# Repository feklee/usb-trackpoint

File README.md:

Introduction
============

Electronics Arduino project, to connect an IBM TrackPoint as an external
pointing device via USB.

Features:

  * TrackPoint fully works, incl. buttons.

  * Adjustable sensitivity with potentiometer.

  * Middle button scrolling.

  * An RGB LED cycles, showing how the program loops.

Circuit
=======

![Photos of circuit, front and back][4]

For the schematic, see the included [EAGLE][2] project.

The PS/2 connection is done with a detachable cable. This allows:

  * testing the Arduino code with an external PS/2 mouse,
  
  * using the TrackPoint as a PS/2 mouse directly on a computer (didn't get
    that to work).

Some components were recycled:

  * TrackPoint board: Broken off from the keyboard of an iSeries 1200
    (1161-267), my first ThinkPad (bought in 2000).

  * Button switches: Taken from an old Logitech mouse.
  
  * PS/2 cable: Cut off an old and broken Cherry keyboard.
  
  * Back metal plate: From the keyboard that provided the TrackPoint board.
  
  * Front metal plate: Cut from a plate found inside a ThinkPad X41, then
    drilled.
  
  * M2 screws: From some ThinkPad.
  
  * M2 nuts: Insert nuts found in ThinkPad X41 plastic parts.

For cycling the RGB LED, a decade counter is used, partly as an exercise for
the author.

Arduino code
============

See comments at top of `.ino` file.

Trackpoint PCB
==============

To figure out the pinout of the TrackPoint PCB, the key steps were:

  * I looked at the FFC connecting the ThinkPad's mainboard, the keyboard, and
    the TrackPoint:
    
      + Two wires were dimensioned wider: power supply
      
      + Three lines lead into the keyboard: TrackPoint buttons

  * Using a multimeter and the ThinkPad turned on, I checked the voltage of the
    power supply wires in the FFC: One is ground, one +5V.

  * I connected the broken off board using individual wires to the ThinkPad. By
    trial and error, I figured out that in addition to the power supply, three
    wires are needed (CLK, DATA, RESET).
    
    Fortunately, the keyboard/TrackPoint FCB receptacles in this ThinkPad are
    big enough to hold the FFC plus 0.3 mm copper wire.

  * With the TrackPoint board connected to an Arduino, I figured out by trial
    and error:
    
      + Which wire is CLK, which one is DATA, and which one is RESET?
      
      + Which of the button wires is for LEFT, which one for RIGHT, which one
        for MIDDLE?

TrackPoint PCB soldered to board with 0.3 mm enameled copper wire:

![Photo of TrackPoint on board][1]

License
=======

Copyright (C) 2013 [Felix E. Klee](mailto:felix.klee@inka.de)

Permission is hereby granted, free of charge, to any person obtaining a copy of
this software and associated documentation files (the "Software"), to deal in
the Software without restriction, including without limitation the rights to
use, copy, modify, merge, publish, distribute, sublicense, and/or sell copies
of the Software, and to permit persons to whom the Software is furnished to do
so, subject to the following conditions:

The above copyright notice and this permission notice shall be included in all
copies or substantial portions of the Software.

THE SOFTWARE IS PROVIDED "AS IS", WITHOUT WARRANTY OF ANY KIND, EXPRESS OR
IMPLIED, INCLUDING BUT NOT LIMITED TO THE WARRANTIES OF MERCHANTABILITY,
FITNESS FOR A PARTICULAR PURPOSE AND NONINFRINGEMENT. IN NO EVENT SHALL THE
AUTHORS OR COPYRIGHT HOLDERS BE LIABLE FOR ANY CLAIM, DAMAGES OR OTHER
LIABILITY, WHETHER IN AN ACTION OF CONTRACT, TORT OR OTHERWISE, ARISING FROM,
OUT OF OR IN CONNECTION WITH THE SOFTWARE OR THE USE OR OTHER DEALINGS IN THE
SOFTWARE.

[1]: images/2013-08-16+02_TrackPoint_annotated.png
[2]: http://en.wikipedia.org/wiki/EAGLE
[3]: https://github.com/feklee/arduino-trackpoint
[4]: images/2013-08-16+02_circuit.jpg

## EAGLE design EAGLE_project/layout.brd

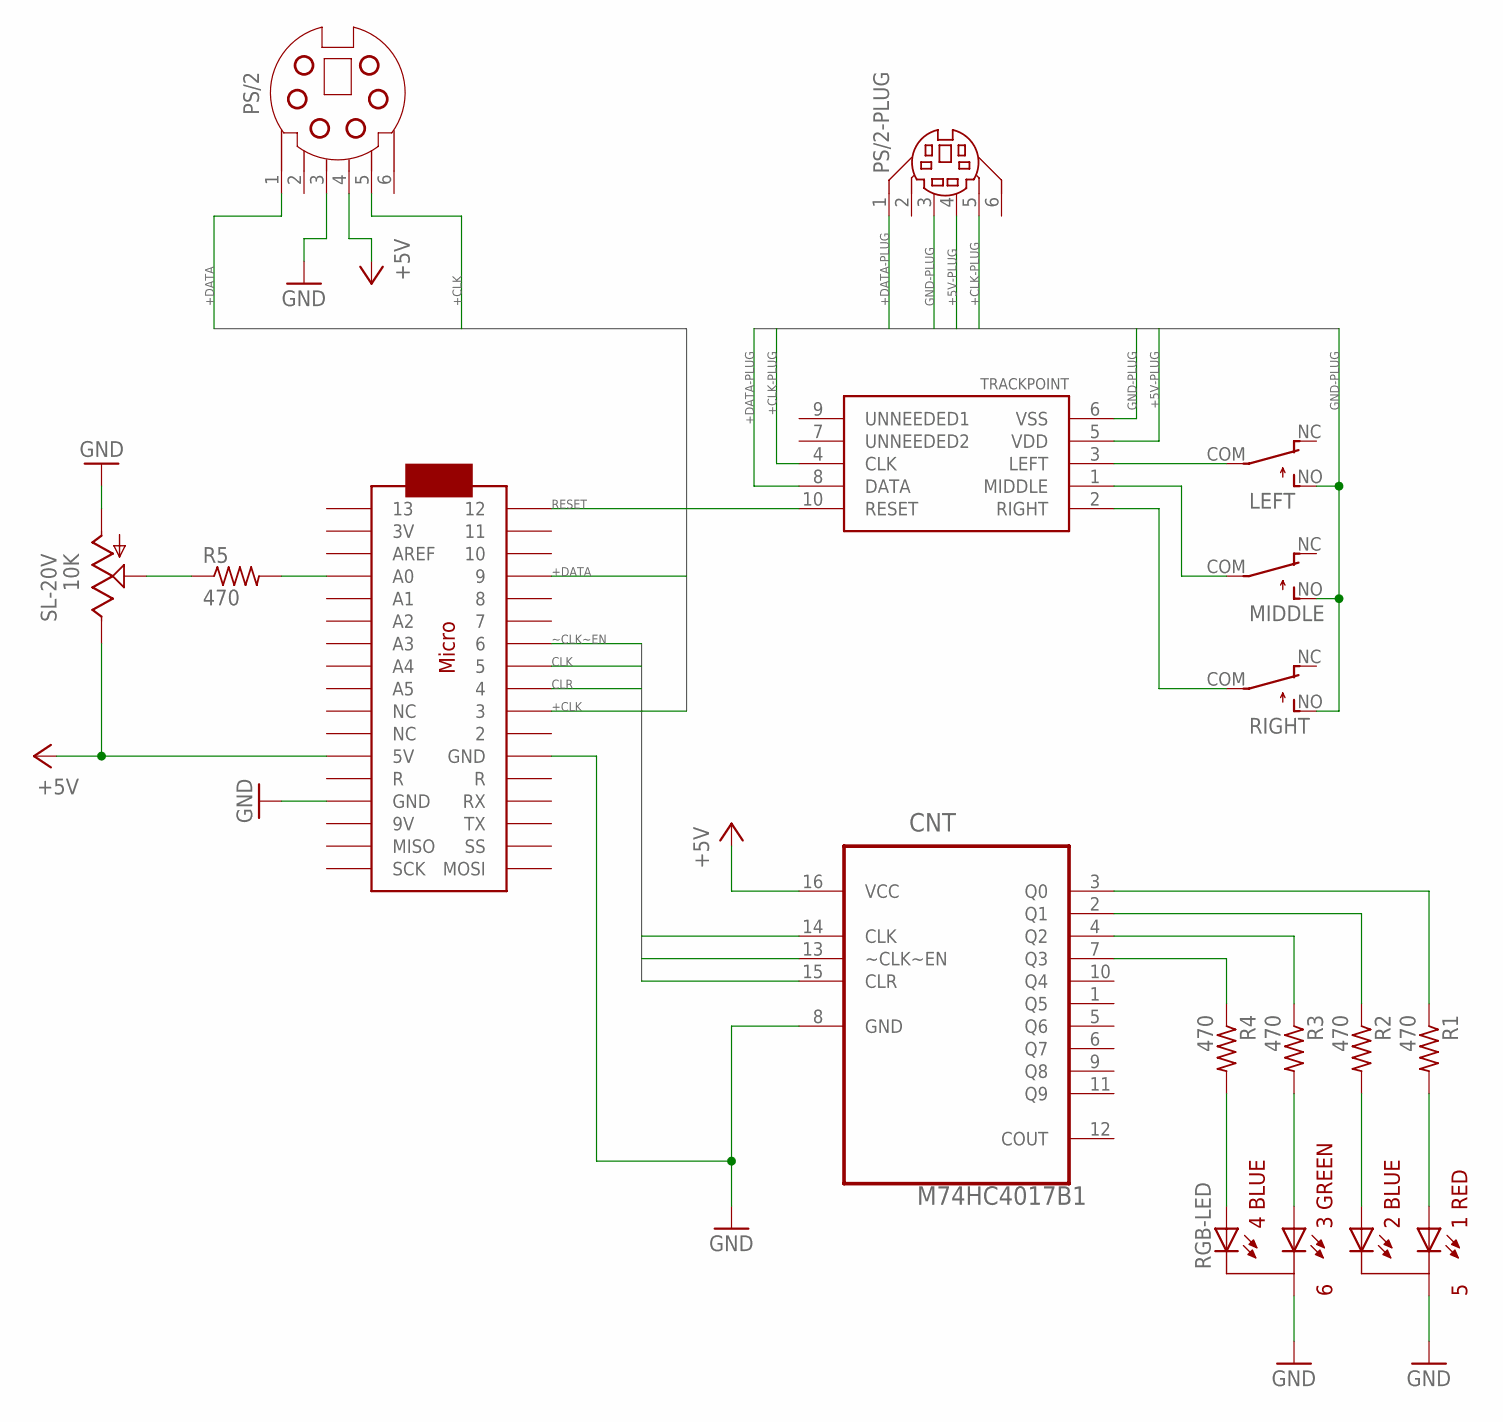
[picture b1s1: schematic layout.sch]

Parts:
CNT: M74HC4017B1; DIP254P762X510-16
PS/2: SSV-BC06
PS/2-PLUG: MDIN06K
R1, R2, R3, R4, R5: 470; 0207/10
RGB-LED: RGBLED; RGBLED5MM
TRACKPOINT: BOARD
U$1: LEFT; D2F
U$2: ARDUINOMICRO
U$3: MIDDLE; D2F
U$5: RIGHT; D2F
U$6: 10K; SL-20V

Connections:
+5V: CNT.16 (VCC), PS/2.4, U$2.P$23 (5V), U$6.4 (E)
+5V-PLUG: PS/2-PLUG.4, TRACKPOINT.5 (VDD)
+CLK: PS/2.5, U$2.P$10 (3)
+CLK-PLUG: PS/2-PLUG.5, TRACKPOINT.4 (CLK)
+DATA: PS/2.1, U$2.P$4 (9)
+DATA-PLUG: PS/2-PLUG.1, TRACKPOINT.8 (DATA)
CLK: CNT.14 (CLK), U$2.P$8 (5)
CLR: CNT.15 (CLR), U$2.P$9 (4)
GND: CNT.8 (GND), PS/2.3, RGB-LED.C5, RGB-LED.C6, U$2.P$12 (GND), U$2.P$21 (GND), U$6.1 (A)
GND-PLUG: PS/2-PLUG.3, TRACKPOINT.6 (VSS), U$1.NO (S), U$3.NO (S), U$5.NO (S)
LED: R4.2, RGB-LED.A4_BLUE
LEFT: TRACKPOINT.3 (LEFT), U$1.COM
unnamed: CNT.2 (Q1), R2.1
unnamed: CNT.3 (Q0), R1.1
unnamed: CNT.4 (Q2), R3.1
unnamed: CNT.7 (Q3), R4.1
unnamed: R5.2, U$2.P$31 (A0)
unnamed: R3.2, RGB-LED.A3_GREEN
unnamed: R2.2, RGB-LED.A2_BLUE
unnamed: R1.2, RGB-LED.A1_RED
unnamed: TRACKPOINT.1 (MIDDLE), U$3.COM
unnamed: TRACKPOINT.2 (RIGHT), U$5.COM
unnamed: R5.1, U$6.2 (S), U$6.3 (S)
RESET: TRACKPOINT.10 (RESET), U$2.P$1 (12)
~CLK~EN: CNT.13 (~CLK~EN), U$2.P$7 (6)

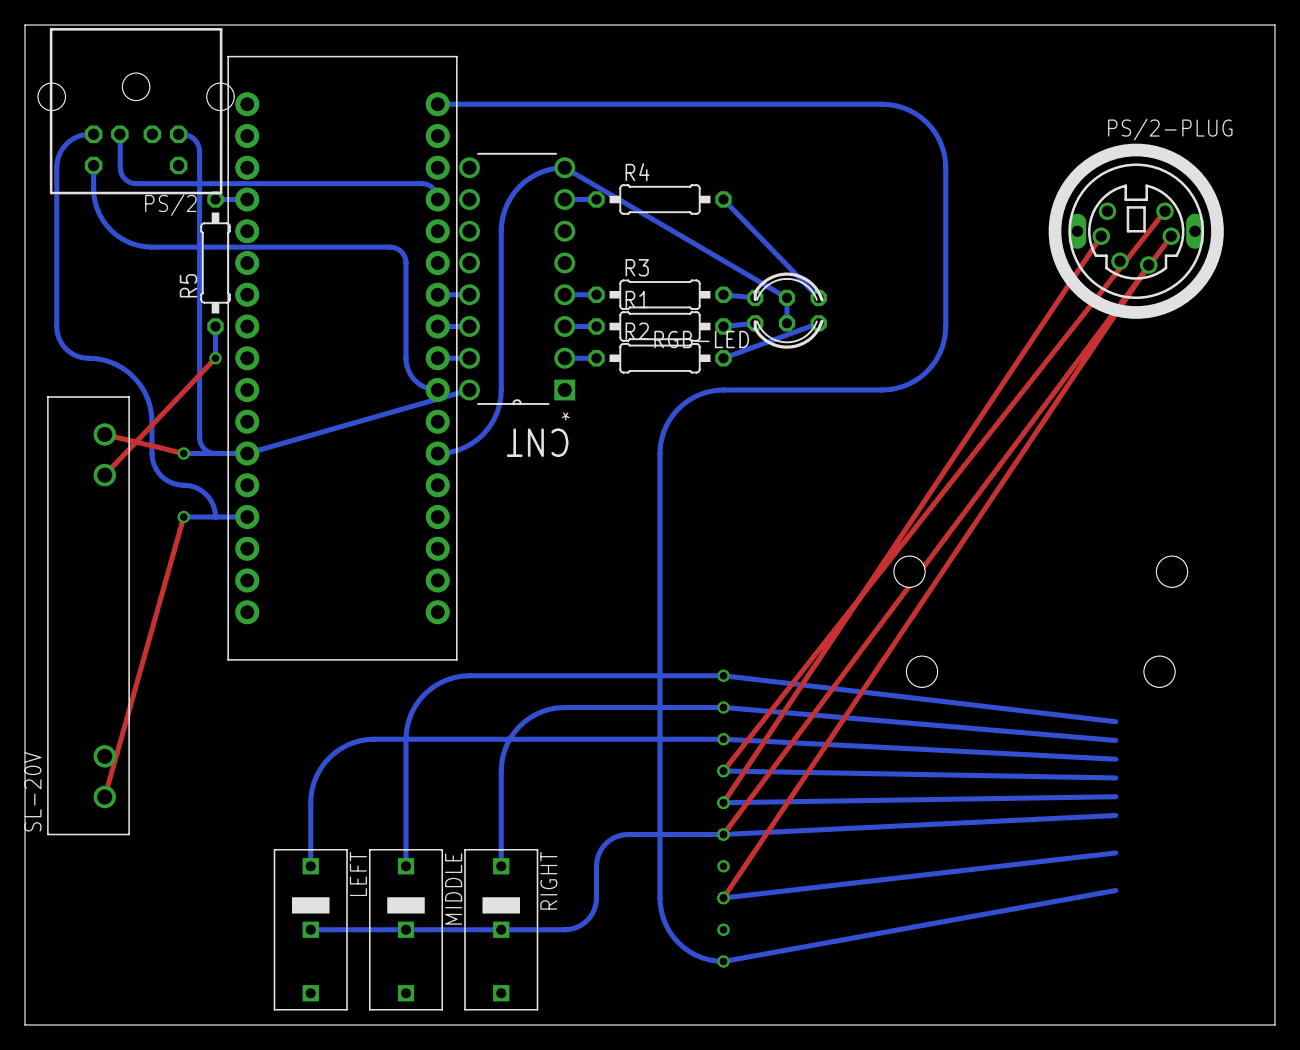
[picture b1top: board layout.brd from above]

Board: 2 copper layers, 100.0 x 80.0 mm, 15 parts (1 on the bottom side), 25 nets.

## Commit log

2013-08-16 Update documentation; Add EAGLE project
2013-08-16 Add Arduino code; Update documentation
2013-08-16 Update directory structure
2013-08-16 Update documentation
2013-08-16 Add source of PS/2 plug
2013-08-16 Remove unused code
2013-08-16 Clean up documentation, code
2013-08-16 Remove hyphen in .ino file name
2013-08-16 Add details to documentation
2013-08-16 Move circuit photos up
2013-08-16 Fix typo
2013-08-17 Extend documentation
2014-03-16 Change TrackPoint CLK from Arduino pin 8 to 7
    This is to have it on an interrupt, necessary for stream mode.
2014-03-16 Change TrackPoint CLK from Arduino pin 7 to 3
    With pin 7, when lifting the finger from the TrackPoint, then cursor movement
    doesn't stop. This happens with the following library and the issue is
    confirmed by its author.
    https://github.com/rampadc/arduino-trackpoint-extended
